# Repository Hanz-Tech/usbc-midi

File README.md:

# Portable USB-MIDI-CV Converter

Ultraportable device for converting MIDI between various hardware standard

Allows you to convert signal between MIDI USB Device, MIDI USB host, MIDI TRS and CV.

## Features
* 1x1 MIDI TRS interface
* Tiny footprint (3cm x 3cm x 1cm)
* USB-C powered
* MIDI USB-MIDI compliant Device
* Plug and play - no drivers needed
* Can act USB host for USB MIDI keyboards, synths....
* Optoisolated TRS MIDI input
* Buffered TRS MIDI output
* CV (0-5 V)
* Powered by RP2040

## Photos

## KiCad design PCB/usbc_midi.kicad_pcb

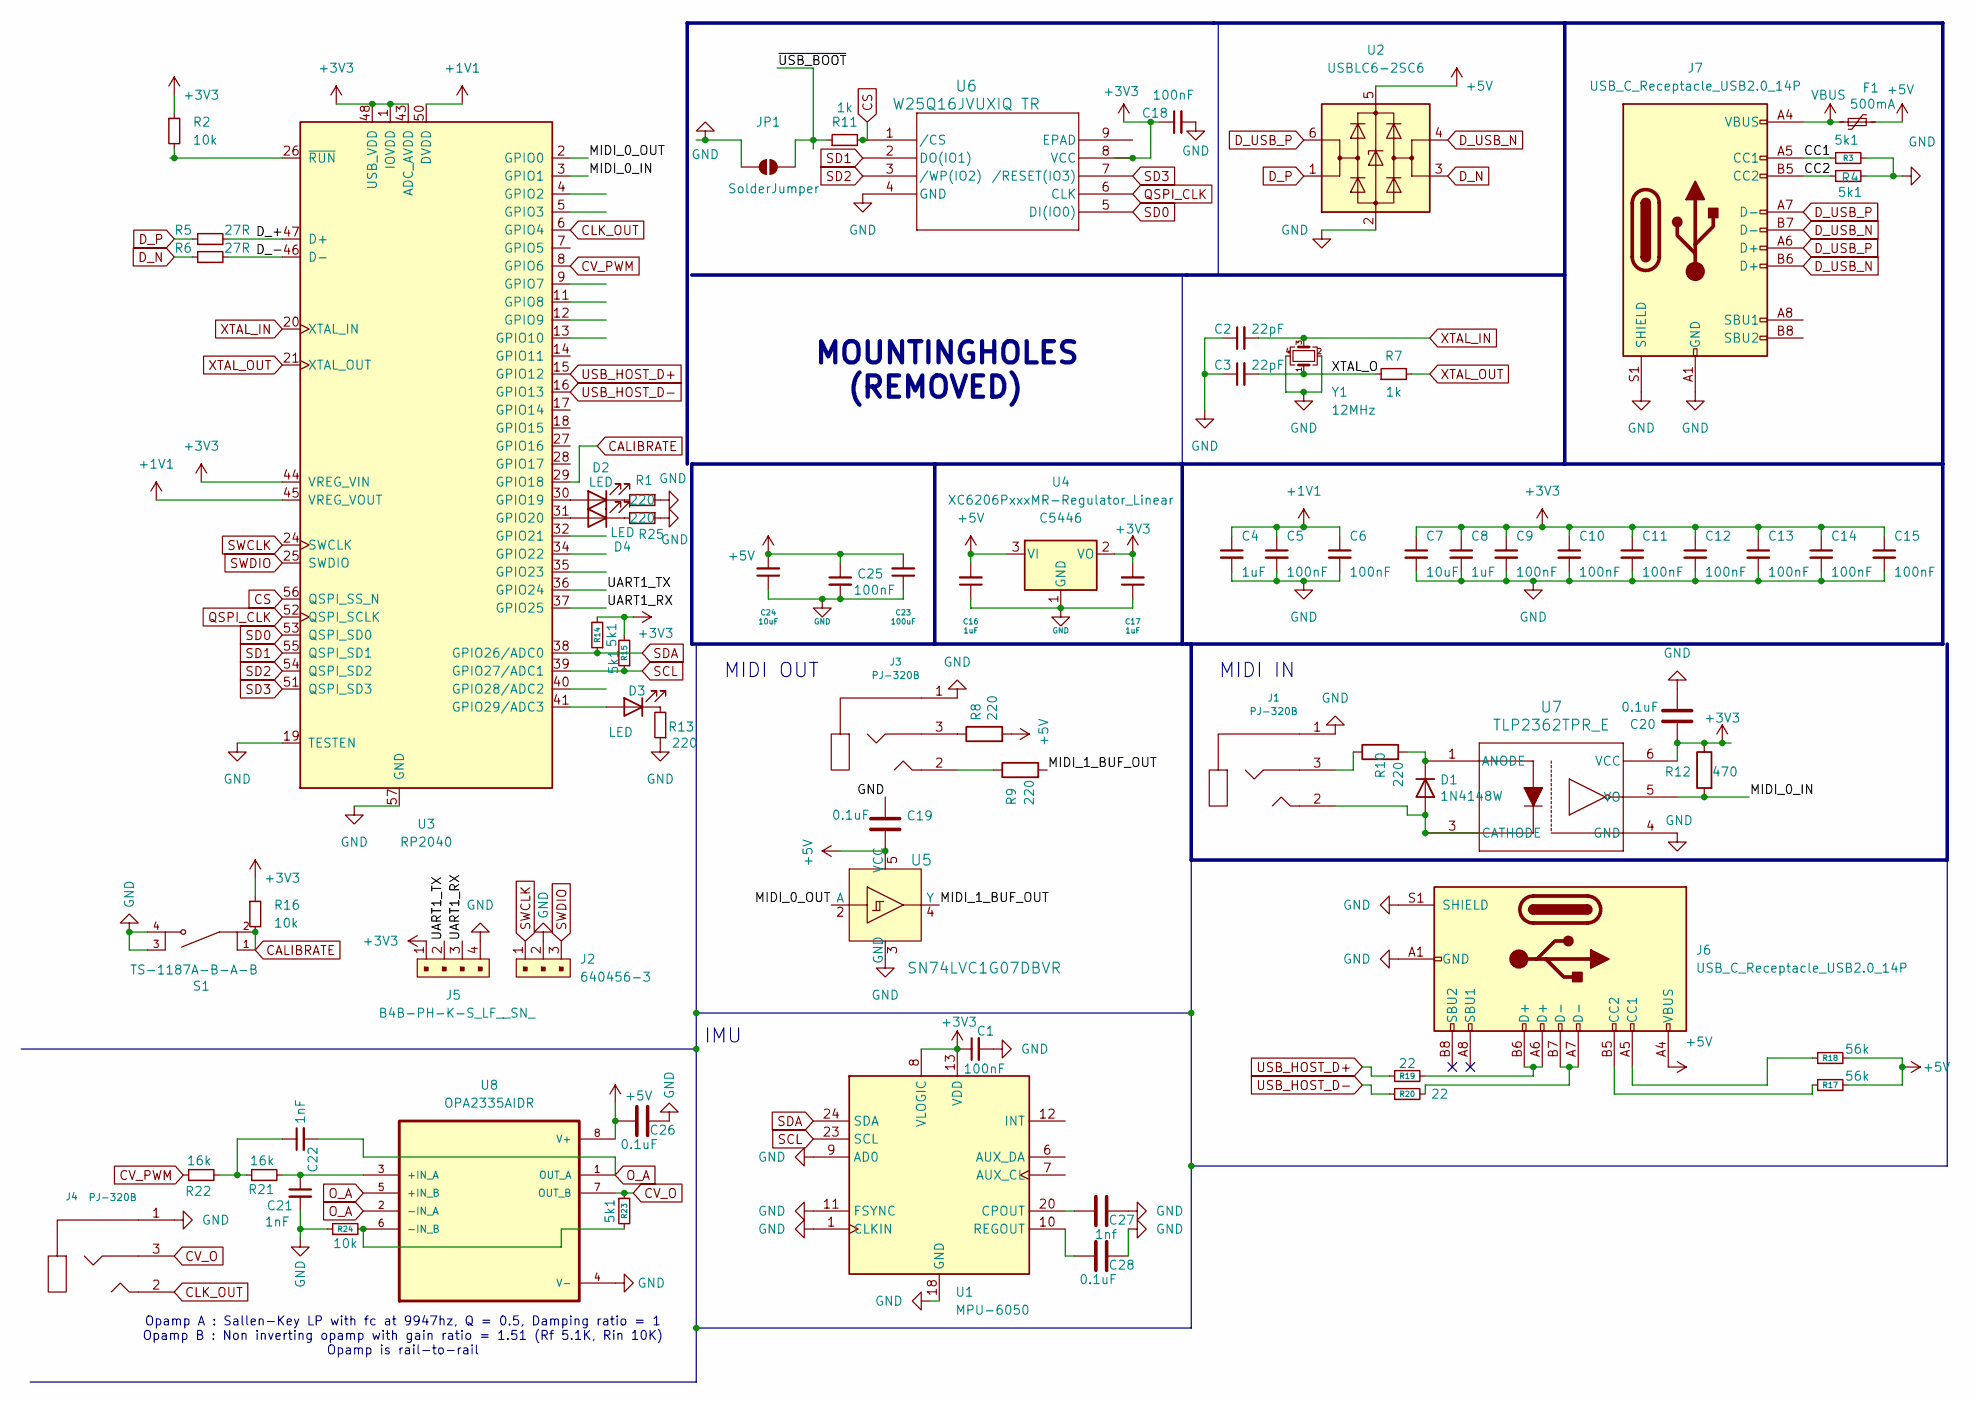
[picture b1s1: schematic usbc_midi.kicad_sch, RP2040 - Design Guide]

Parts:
C1, C5, C6, C9, C10, C11, C12, C13, C14, C15, C18, C25: 100nF; C_0402_1005Metric; LCSC C1525
C2, C3: 22pF; C_0402_1005Metric; LCSC C1555
C4, C8, C16, C17: 1uF; C_0402_1005Metric; LCSC C52923
C7: 10uF; C_0402_1005Metric; LCSC C15525
C19, C20, C26, C28: 0.1uF; C_0402_1005Metric; LCSC C1525
C21, C22: 1nF; C_0402_1005Metric; LCSC C1523
C23: 100uF; C_1206_3216Metric; LCSC C15008
C24: 10uF; C_0603_1608Metric; LCSC C19702
C27: 1nf; C_0402_1005Metric; LCSC C1523
D1: 1N4148W; D_SOD-123; LCSC C81598
D2, D3, D4: LED; D_0603_1608Metric_Pad1.05x0.95mm_HandSolder; LCSC C2286
F1: 500mA; Fuse_1206_3216Metric; LCSC C70077
J1, J3, J4: PJ-320B; 3.5mm_stereo_jack_PJ320B_no_back_hole; LCSC C2884998
J2: 640456-3; PinHeader_1x03_P1.00mm_Vertical; MPN 640456-3; Digi-Key_PN A19470-ND
J5: B4B-PH-K-S_LF__SN_; PinHeader_1x04_P1.00mm_Vertical; MPN B4B-PH-K-S(LF)(SN); Digi-Key_PN 455-1706-ND
J6, J7: USB_C_Receptacle_USB2.0_14P; USB_C_Receptacle_HRO_TYPE-C-31-M-12; LCSC C165948
JP1: SolderJumper; SolderJumper-2_P1.3mm_Open_RoundedPad1.0x1.5mm
R1, R8, R9, R10, R13, R25: 220; R_0402_1005Metric; LCSC C25091
R2, R16, R24: 10k; R_0402_1005Metric; LCSC C25744
R3, R4, R14, R15, R23: 5k1; R_0402_1005Metric; LCSC C25905
R5, R6: 27R; R_0603_1608Metric; LCSC C25190
R7, R11: 1k; R_0402_1005Metric; LCSC C11702
R12: 470; R_0603_1608Metric_Pad0.98x0.95mm_HandSolder; LCSC C17710
R17, R18: 56k; R_0603_1608Metric; LCSC C23206
R19, R20: 22; R_0402_1005Metric; LCSC C25092
R21, R22: 16k; R_0402_1005Metric; LCSC C25759
S1: TS-1187A-B-A-B; TACTILE_SWITCH_SMD_5.2MM; PARTREV A0; LCSC C318884
U1: MPU-6050; InvenSense_QFN-24_4x4mm_P0.5mm; LCSC C24112
U2: USBLC6-2SC6; SOT-23-6; LCSC C2827654
U3: RP2040; RP2040-QFN-56; LCSC C2040
U4: XC6206PxxxMR-Regulator_Linear; SOT-23; LCSC C5446
U5: SN74LVC1G07DBVR; SOT-23-5; Digi-Key_PN 296-8485-1-ND
U6: W25Q16JVUXIQ TR; W25Q16JVUXIQ; LCSC C2843335
U7: TLP2362TPR_E; tlp2362; LCSC C37658
U8: OPA2335AIDR; SOIC127P599X175-8N; LCSC C41618
Y1: 12MHz; Crystal_SMD_3225-4Pin_3.2x2.5mm; LCSC C9002

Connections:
+1V1: C4.1, C5.1, C6.1, U3.23 (DVDD), U3.45 (VREG_VOUT), U3.50 (DVDD)
+3V3: C1.1, C7.1, C8.1, C9.1, C10.1, C11.1, C12.1, C13.1, C14.1, C15.1, C17.2, C18.1, C20.1, J5.1, R2.1, R12.1, R14.2, R15.2, R16.1, U1.8 (VLOGIC), U1.13 (VDD), U3.1 (IOVDD), U3.10 (IOVDD), U3.22 (IOVDD), U3.33 (IOVDD), U3.42 (IOVDD), U3.43 (ADC_AVDD), U3.44 (VREG_VIN), U3.48 (USB_VDD), U3.49 (IOVDD), U4.2 (VO), U6.8 (VCC), U7.6 (VCC)
+5V: C16.2, C19.2, C23.2, C24.2, C25.1, C26.1, F1.2, J6.A4 (VBUS), J6.A9 (VBUS), J6.B4 (VBUS), J6.B9 (VBUS), R8.2, R17.2, R18.2, U2.5 (VBUS), U4.3 (VI), U5.5 (VCC), U8.8 (V+)
/CC1: J7.A5 (CC1), R3.1
/CC2: J7.B5 (CC2), R4.1
/D_+: R5.2, U3.47 (D+)
/D_-: R6.2, U3.46 (D-)
/MIDI_0_IN: R12.2, U3.3 (GPIO1), U7.5 (VO)
/MIDI_0_OUT: U3.2 (GPIO0), U5.2 (A)
/MIDI_1_BUF_OUT: R9.2, U5.4 (Y)
/UART1_RX: J5.3, U3.37 (GPIO25)
/UART1_TX: J5.2, U3.36 (GPIO24)
/XTAL_O: C3.2, R7.1, Y1.1
/~USB_BOOT: JP1.2 (B), R11.1
CALIBRATE: R16.2, S1.1, S1.2, U3.29 (GPIO18)
CLK_OUT: J4.2, U3.6 (GPIO4)
CS: R11.2, U3.56 (QSPI_SS_N), U6.1 (/CS)
CV_O: J4.3, R23.1, U8.7 (OUT_B)
CV_PWM: R22.1, U3.8 (GPIO6)
D_N: R6.1, U2.3 (I/O2)
D_P: R5.1, U2.1 (I/O1)
D_USB_N: J7.B6 (D+), J7.B7 (D-), U2.4 (I/O2)
D_USB_P: J7.A6 (D+), J7.A7 (D-), U2.6 (I/O1)
GND: C1.2, C2.1, C3.1, C4.2, C5.2, C6.2, C7.2, C8.2, C9.2, C10.2, C11.2, C12.2, C13.2, C14.2, C15.2, C16.1, C17.1, C18.2, C19.1, C20.2, C21.2, C23.1, C24.1, C25.2, C26.2, C27.2, C28.2, J1.1, J2.2, J3.1, J4.1, J5.4, J6.A1 (GND), J6.A12 (GND), J6.B1 (GND), J6.B12 (GND), J6.S1 (SHIELD), J7.A1 (GND), J7.A12 (GND), J7.B1 (GND), J7.B12 (GND), J7.S1 (SHIELD), JP1.1 (A), R1.1, R3.2, R4.2, R13.1, R24.1, R25.1, S1.3, S1.4, U1.1 (CLKIN), U1.9 (AD0), U1.11 (FSYNC), U1.18 (GND), U2.2 (GND), U3.19 (TESTEN), U3.57 (GND), U4.1 (GND), U5.3 (GND), U6.4 (GND), U7.4 (GND), U8.4 (V-), Y1.2, Y1.4
unnamed: C22.1, R21.1, R22.2
unnamed: D1.2 (A), J1.2, U7.3 (CATHODE)
unnamed: D1.1 (K), R10.2, U7.1 (ANODE)
unnamed: D2.2 (A), U3.30 (GPIO19)
unnamed: D2.1 (K), R1.2
unnamed: D3.2 (A), U3.41 (GPIO29/ADC3)
unnamed: D3.1 (K), R13.2
unnamed: D4.2 (A), U3.31 (GPIO20)
unnamed: D4.1 (K), R25.2
unnamed: J1.3, R10.1
unnamed: J3.2, R9.1
unnamed: J3.3, R8.1
unnamed: J6.A5 (CC1), R18.1
unnamed: J6.B5 (CC2), R17.1
unnamed: J6.A6 (D+), J6.B6 (D+), R19.2
unnamed: J6.A7 (D-), J6.B7 (D-), R20.2
unnamed: C27.1, U1.20 (CPOUT)
unnamed: C28.1, U1.10 (REGOUT)
unnamed: R2.2, U3.26 (~RUN)
unnamed: C21.1, R21.2, U8.3 (+IN_A)
unnamed: R23.2, R24.2, U8.6 (-IN_B)
O_A: C22.2, U8.1 (OUT_A), U8.2 (-IN_A), U8.5 (+IN_B)
QSPI_CLK: U3.52 (QSPI_SCLK), U6.6 (CLK)
SCL: R15.1, U1.23 (SCL), U3.39 (GPIO27/ADC1)
SD0: U3.53 (QSPI_SD0), U6.5 (DI(IO0))
SD1: U3.55 (QSPI_SD1), U6.2 (DO(IO1))
SD2: U3.54 (QSPI_SD2), U6.3 (/WP(IO2))
SD3: U3.51 (QSPI_SD3), U6.7 (/RESET(IO3))
SDA: R14.1, U1.24 (SDA), U3.38 (GPIO26/ADC0)
SWCLK: J2.1, U3.24 (SWCLK)
SWDIO: J2.3, U3.25 (SWDIO)
USB_HOST_D+: R19.1, U3.15 (GPIO12)
USB_HOST_D-: R20.1, U3.16 (GPIO13)
VBUS: F1.1, J7.A4 (VBUS), J7.A9 (VBUS), J7.B4 (VBUS), J7.B9 (VBUS)
XTAL_IN: C2.2, U3.20 (XTAL_IN), Y1.3
XTAL_OUT: R7.2, U3.21 (XTAL_OUT)

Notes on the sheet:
MIDI IN
Opamp A : Sallen-Key LP with fc at 9947hz, Q = 0.5, Damping ratio = 1 Opamp B : Non inverting opamp with gain ratio = 1.51 (Rf 5.1K, Rin 10K) Opamp is rail-to-rail
MOUNTINGHOLES (REMOVED)
MIDI OUT
IMU

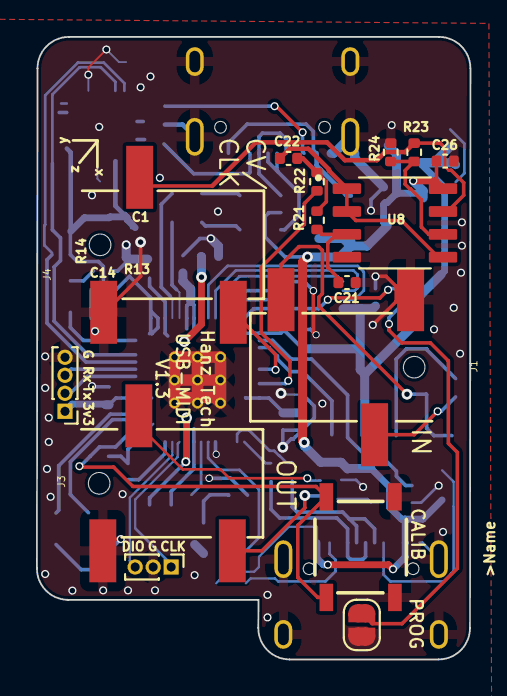
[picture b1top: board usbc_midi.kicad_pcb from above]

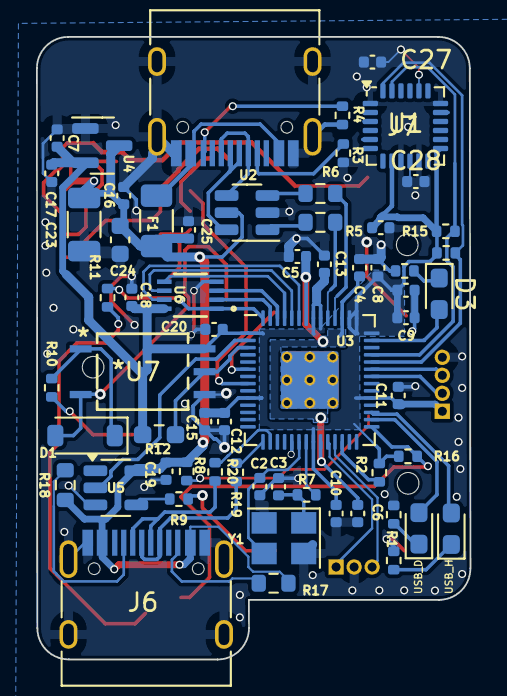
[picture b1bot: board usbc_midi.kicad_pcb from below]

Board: 2 copper layers, 24.1 x 34.6 mm, 76 parts (61 on the bottom side), 60 nets.

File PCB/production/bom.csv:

Designator,Footprint,Quantity,Value,LCSC Part #
"C1, C10, C11, C12, C13, C14, C15, C18, C25, C5, C6, C9",0402,12,100nF,C1525
"C16, C17, C4, C8",0402,4,1uF,C52923
"C19, C20, C26",0402,3,0.1uF, C1525
"C2, C3",0402,2,22pF,C1555
"C21, C22",0402,2,1nF,C1523
C23,1206,1,100uF,C15008
C24,0603,1,10uF,C19702
C7,0402,1,10uF,C15525
D1,D_SOD-123,1,1N4148W,    C81598
"D2, D3",0603,2,LED,C2286
F1,1206,1,500mA,C70077
J2,PinHeader_1x03_P1.00mm_Vertical,1,640456-3,640456-3
J5,PinHeader_1x04_P1.00mm_Vertical,1,B4B-PH-K-S_LF__SN_,B4B-PH-K-S(LF)(SN)
J6,USB_C_Receptacle_HRO_TYPE-C-31-M-12,1,USB_C_Receptacle_USB2.0_14P,C165948
"R1, R10, R13, R8, R9",0402,5,220,C25091
"R11, R7",0402,2,1k,C11702
R12,0603,1,470,C17710 
"R14, R15, R23, R3, R4",0402,5,5k1,C25905
"R16, R2, R24",0402,3,10k,C25744
"R17, R18",0603,2,56k,C23206
"R19, R20",0402,2,22,C25092
"R21, R22",0402,2,16k,C25759
"R5, R6",0603,2,27R,C25190
S1,TACTILE_SWITCH_SMD_5.2MM,1,TS-1187A-B-A-B,C318884
U1,InvenSense_QFN-24_4x4mm_P0.5mm,1,MPU-6050,C24112 
U2,SOT-23-6,1,USBLC6-2SC6,C2827654
U3,RP2040-QFN-56,1,RP2040,C2040
U4,SOT-23,1,XC6206PxxxMR-Regulator_Linear,C5446
U5,SOT-23-5,1,SN74LVC1G07DBVR,C7829
U6,W25Q16JVUXIQ,1,W25Q16JVUXIQ TR,C2843335
U7,tlp2362,1,TLP2362TPR_E,C37658
U8,SOIC127P599X175-8N,1,OPA2335AIDR,    C41618
UNK1,USB-C-SMD_XKB_U261-24XN-4BC2SS,1,USB-C-SMD_XKB_U261-24XN-4BC2SS,C2938597
Y1,Crystal_SMD_3225-4Pin_3.2x2.5mm,1,12MHz,C9002

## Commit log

2025-03-20 routing in progress
2025-03-20 update routing
2025-03-21 finished 1st layout
2025-03-21 fix silkscreen
2025-03-21 add logo
2025-03-22 ready v1
2025-03-22 export v1.0
2025-03-23 cleanup
2025-03-25 added layout for cv control
2025-03-26 fix some routing errors
2025-03-28 1.2 added usb host
2025-03-29 1.2 sent to production
2025-04-01 add photos, update readme
2025-04-14 switched usb male to usb c female
2025-05-24 Add new led, update IMU routing
2025-08-05 add missing caps on imu
